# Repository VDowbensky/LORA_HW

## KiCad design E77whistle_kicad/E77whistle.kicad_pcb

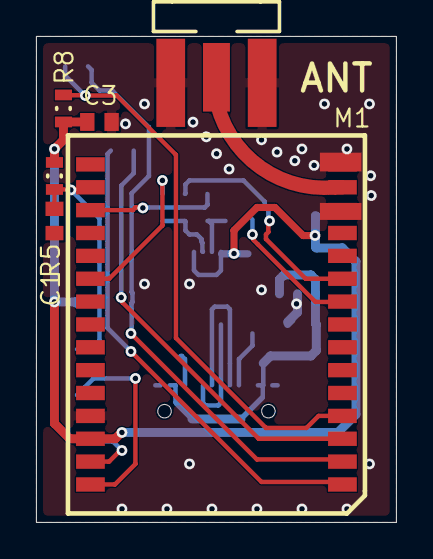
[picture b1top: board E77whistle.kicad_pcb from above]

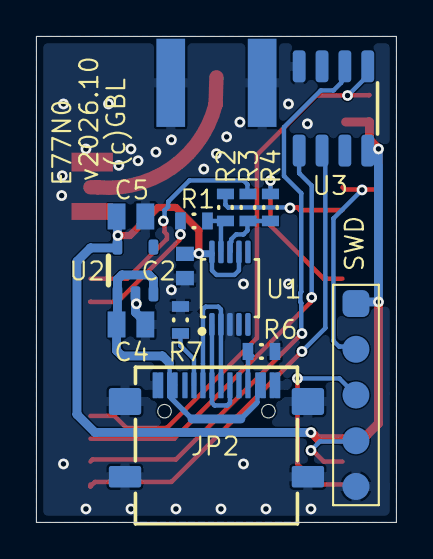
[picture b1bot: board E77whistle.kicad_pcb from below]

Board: 2 copper layers, 20.0 x 27.0 mm, 20 parts (14 on the bottom side), 21 nets.

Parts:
C1, C2, C3: 100nF; C-0603
C4, C5: 10uF; C-0805
JP1: EM-SA071-GGT; SMA_F_EDGE
JP2: L-KLS1-5473
JP3: HEADER 5; PLS1-5_SMD
M1: E77-400M22S; E77XX-M22
R1, R2, R3, R4: nc; R-0603
R5: 10k; R-0603
R6, R7: 5k1; R-0603
R8: 100k; R-0603
U1: CH340E; MSOP-10
U2: LP5907MFX-3.0; SOT-23-5
U3: W25Q64FV; SO-8

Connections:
DN: JP2.A7, JP2.B7, U1.2
DP: JP2.A6, JP2.B6, U1.1
FLASH_CE: M1.4, R8.1, U3.1
GND: C1.1, C2.1, C3.1, C4.2, C5.2, JP1.2, JP2.1, JP2.A1, JP2.A12, JP2.B1, JP2.B12, JP3.5, M1.13, M1.15, M1.27, R6.2, R7.2, U1.3, U2.2, U3.4
MISO: M1.2, U3.2
MOSI: M1.3, U3.5
NRST: C1.2, JP3.2, M1.17, R5.1
NetJP1_1: JP1.1, M1.14
NetJP2_A5: JP2.A5, R7.1
NetJP2_B5: JP2.B5, R6.1
PA2: M1.9, R1.1
PA3: M1.10, R3.1
PA9: M1.18, R2.1
PA10: M1.21, R4.1
RXD: R3.2, R4.2, U1.8
SCK: M1.1, U3.6
SWCLK: JP3.3, M1.30
SWDIO: JP3.4, M1.29
TXD: R1.2, R2.2, U1.9
VBUS: C4.1, JP2.A4, JP2.A9, JP2.B4, JP2.B9, U2.1, U2.3
VCC: C2.2, C3.2, C5.1, JP3.1, M1.28, R5.2, R8.2, U1.7, U1.10, U2.5, U3.8
